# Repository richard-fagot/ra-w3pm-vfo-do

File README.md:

**TODO : Ajouter le sketch de l'arduino pour être sûr qu'il soit disponible.**
# Oscillateur à fréquence variable asservi par GPS de 1 à 112,5MHz
Ultra précis (0.1Hz avec le module GPS) cet oscillateur à signaux carrés programmable dispose de deux sorties d'horloge.

Ce projet propose un PCB compact, s'enfichant à l'arrière du LCD et supportant le l'oscillateur SI5351. **TODO : Le GPS est relié par des câbles ?**.

Ce PCB repose sur le [schéma créé par W3PM](http://www.knology.net/~gmarcus/Si5351/Si5351_VFO_QEX.pdf) (voir la [page de l'auteur](http://www.knology.net/~gmarcus/)).

# Réalisation

Après avoir fait réaliser le PCB, souder les composants dans cet ordre :

## Alimentation
Souder les composants dans cet ordre :
- C3, C4, C5 et C6 ;
- D1 ;
- U1 (utiliser une panne plate et large pour le GND).

Vérifier que l'alimenation de la carte est correctement régulée en appliquant une tension d'au moins 10V au niveau de l'emplacement du connecteur J9. La tension mesurée au pin *+5V* à l'emplacement du connecteur GPS doit être de 5V.

Si ce n'est pas le cas, mesurer la tension entre la sortie de U1 et sa patte dissipateur/GND :
- Si elle est différente de 5V c'est qu'au moins un des condensateurs C3, C4, C5 ou C6 est défectueux ou de mauvaise valeur ;
- Si elle vaut 5V c'est que la soudure du GND n'est pas correctement réalisée.

Éviter de souder l'arduino directement, utiliser plutôt des connecteurs.

# BOM

L'ensemble des composants coûte environ 30€ hors boitier et PCB.

| Référence | Quantité | Valeur | Source | Prix |
|----|-----|-----|-----|-----|
| C1, C2, C4, C5 | 4 | 0.1µF boitier CMS 0805 || 0,04€ |
| C3, C6 | 2 | 4.7µF boitier CMS 0805 || 0,02€ |
| J2, J3, J4, J9 | 4 | Connecteur dupont mâle vertical 1x2 broches pas 2,54 mm || 0,04€ |
| J1 | 1 | Connecteur dupont mâle vertical 1x3 broches pas 2,54 mm || - |
| J5 | 1 | Connecteur dupont femelle vertical 1x7 broches pas 2,54 mm || 1,00€ |
| J10 | 1 | Connecteur dupont femelle vertical 1x4 broches pas 2,54 mm || 1,00€ |
| J8 | 1 | Connecteur dupont femelle vertical 1x16 broches pas 2,54 mm || 1,00€ |
| D1 | 1 | Diode schottky boitier CMS SS24 || 0,0299€ |
| U1 | 1 | Régulateur linéaire L78M05 boitier CMS TO-252 || 0,189€|
| RV1, RV2 | 1 | potentiomètre 10k boitier CMS 3x3 || 0,216€ |
| A1 | 1 | Arduino nano v3.0|| 1,70€|
| LCD | 1 | Écran LCD 16x2 à controlleur HD44780 || 5,00€ |
| SI5351 | 1 | Module SI5351 à 7 broches || 6,00€ |
| GPS | 1 | Module GPS avec antenne || 15,00€ |
| Boutons poussoir | 3 ||| 1,50€ |
| Encodeur rotatif | 1 | Encodeur rotatif avec son bouton || 0,50€ |
| Coaxial | qsp | Câble coaxial RG316 || 0,50€|
| Boitier |||||

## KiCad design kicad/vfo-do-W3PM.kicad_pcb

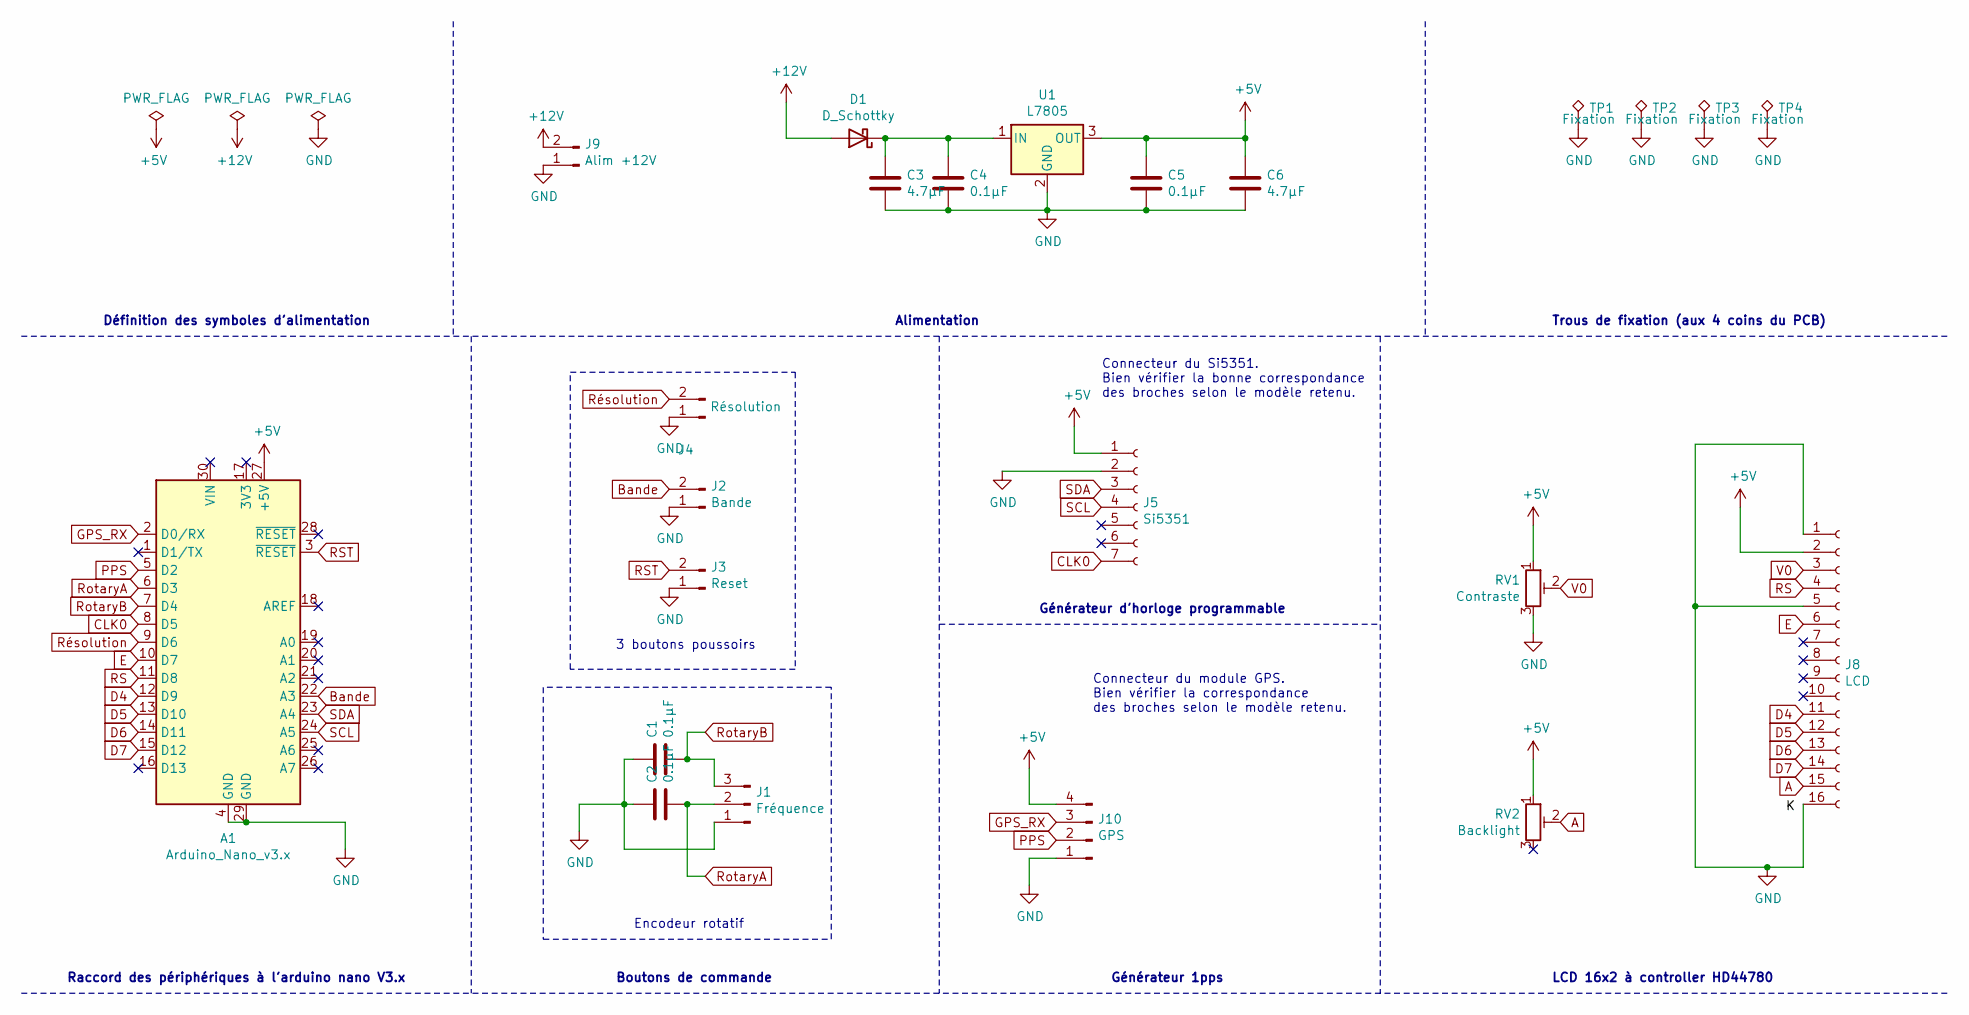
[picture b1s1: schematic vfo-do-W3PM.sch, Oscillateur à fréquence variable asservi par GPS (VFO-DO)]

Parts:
A1: Arduino_Nano_v3.x; Arduino_Nano
C1, C2, C4, C5: 0.1µF; C_0805_2012Metric
C3, C6: 4.7µF; C_0805_2012Metric
D1: D_Schottky; D_SMA
J1: Fréquence; PinHeader_1x03_P2.54mm_Vertical
J2: Bande; PinHeader_1x02_P2.54mm_Vertical
J3: Reset; PinHeader_1x02_P2.54mm_Vertical
J4: Résolution; PinHeader_1x02_P2.54mm_Vertical
J5: Si5351; PinSocket_1x07_P2.54mm_Vertical
J8: LCD; PinSocket_1x16_P2.54mm_Vertical
J9: Alim +12V; PinHeader_1x02_P2.54mm_Vertical
J10: GPS; PinHeader_1x04_P2.54mm_Vertical
RV1: Contraste; trimmer_3x3
RV2: Backlight; trimmer_3x3
TP1, TP2, TP3, TP4: Fixation; MountingHole_3.2mm_M3_Pad_Via
U1: L7805; TO-252-2

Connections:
+5V: A1.27 (+5V), C5.1, C6.1, J5.1, J8.2, J10.4, RV1.1, RV2.1, U1.3 (OUT)
+12V: D1.2 (A), J9.2
A: J8.15, RV2.2
Bande: A1.22 (A3), J2.2
CLK0: A1.8 (D5), J5.7
D4: A1.12 (D9), J8.11
D5: A1.13 (D10), J8.12
D6: A1.14 (D11), J8.13
D7: A1.15 (D12), J8.14
E: A1.10 (D7), J8.6
GND: A1.4 (GND), A1.29 (GND), C1.1, C2.1, C3.2, C4.2, C5.2, C6.2, J1.1, J2.1, J3.1, J4.1, J5.2, J8.1, J8.5, J8.16, J9.1, J10.1, RV1.3, TP1.1, TP2.1, TP3.1, TP4.1, U1.2 (GND)
GPS_RX: A1.2 (D0/RX), J10.3
unnamed: C3.1, C4.1, D1.1 (K), U1.1 (IN)
PPS: A1.5 (D2), J10.2
RS: A1.11 (D8), J8.4
RST: A1.3 (~RESET), J3.2
RotaryA: A1.6 (D3), C2.2, J1.2
RotaryB: A1.7 (D4), C1.2, J1.3
Résolution: A1.9 (D6), J4.2
SCL: A1.24 (A5), J5.4
SDA: A1.23 (A4), J5.3
V0: J8.3, RV1.2

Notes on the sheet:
Définition des symboles d'alimentation
Alimentation
Trous de fixation (aux 4 coins du PCB)
3 boutons poussoirs
Encodeur rotatif
Boutons de commande
Connecteur du Si5351. Bien vérifier la bonne correspondance des broches selon le modèle retenu.
Connecteur du module GPS. Bien vérifier la correspondance des broches selon le modèle retenu.
Générateur d'horloge programmable
Générateur 1pps
LCD 16x2 à controller HD44780
Raccord des périphériques à l'arduino nano V3.x

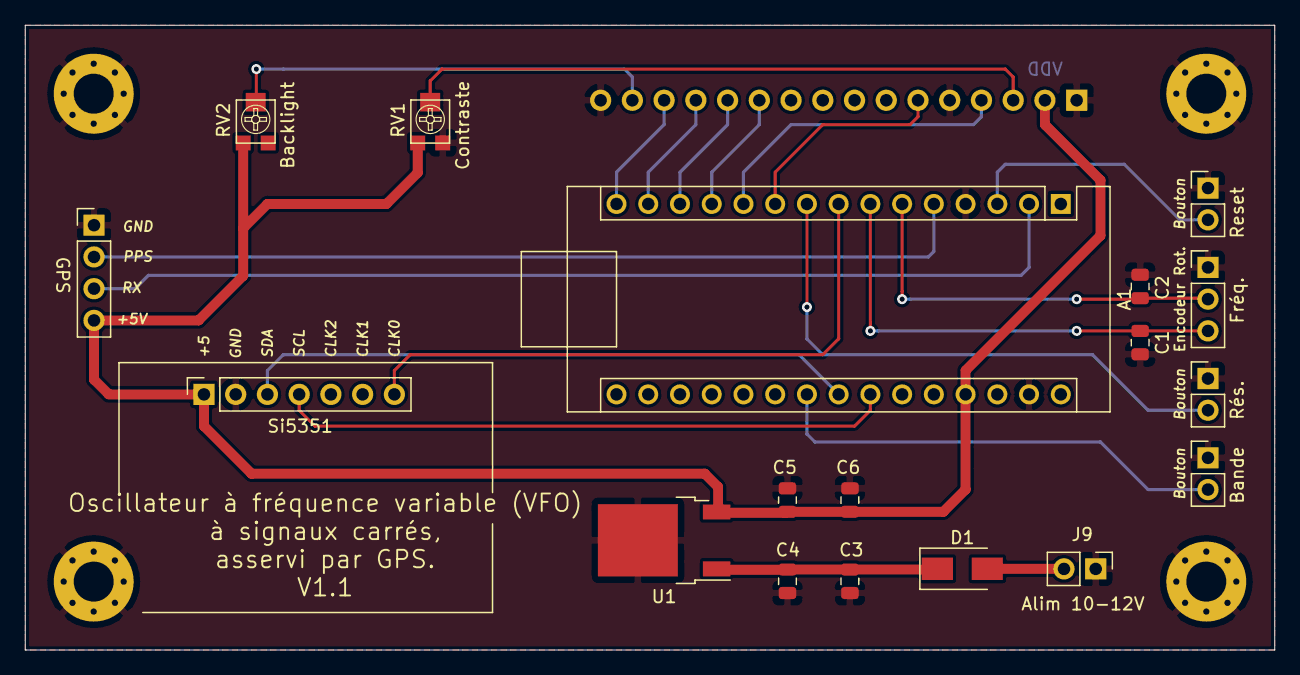
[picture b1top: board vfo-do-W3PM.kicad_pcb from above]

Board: 2 copper layers, 100.0 x 50.0 mm, 23 parts (1 on the bottom side), 22 nets.

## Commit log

2020-08-23 Nouveau design PCB avec les conseils du discord
2020-08-24 Amélioration du routage, perçage de fixation
2020-08-25 plaque standard 10x5
2020-09-11 Ajout des bonnes empreintes pour les trimmers
2020-09-12 Réorganisation du projet + début doc
2020-09-12 typo
2020-10-09 Fix sens connecteur LCD
